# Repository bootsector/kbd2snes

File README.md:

# kbd2snes
PS/2 keyboard to Super Nintendo Adapter

http://www.brunofreitas.com/node/71

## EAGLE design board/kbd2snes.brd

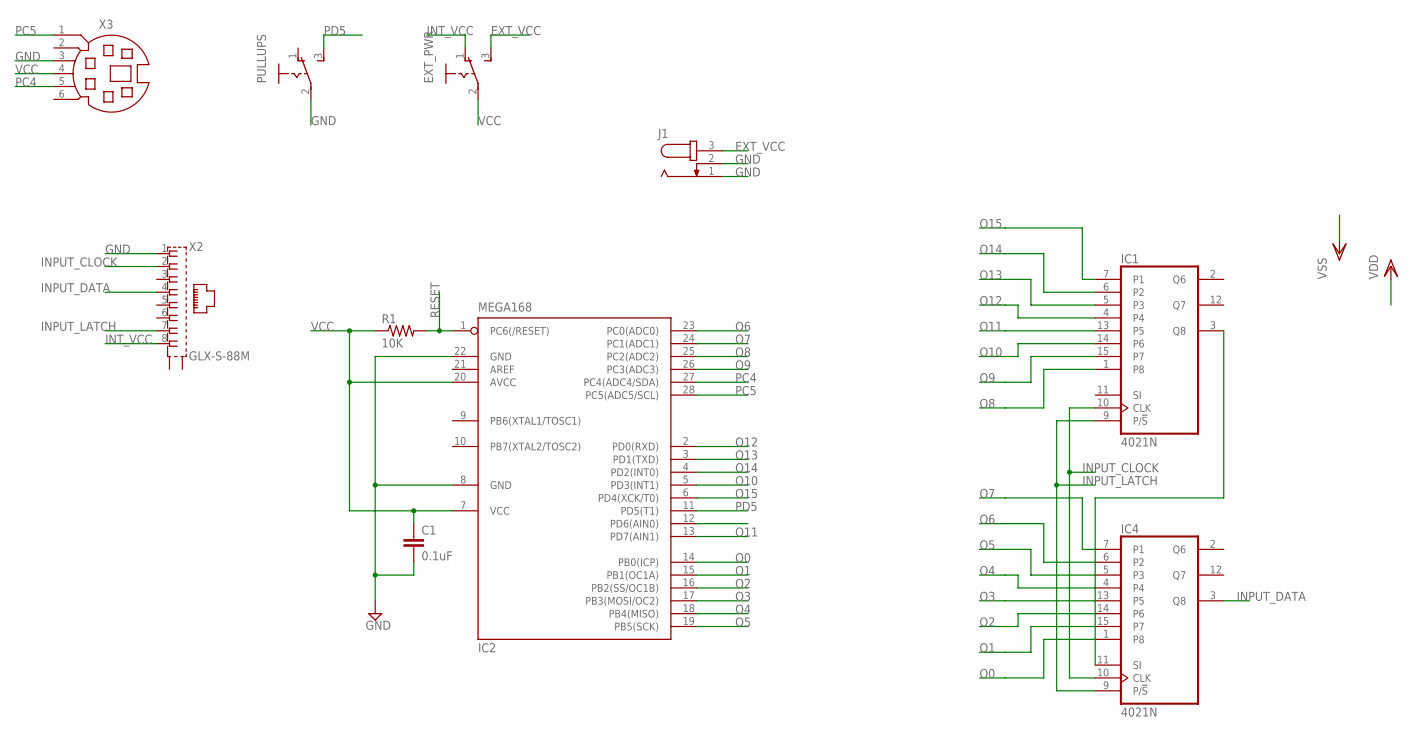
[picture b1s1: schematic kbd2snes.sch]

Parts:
C1: 0.1uF; C050-024X044
EXT_PWR: CHAVE
IC1, IC4: 4021N; DIL16
IC2: MEGA168; DIL28-3
J1: JACK-PLUG1; SPC4078
PULLUPS: CHAVE
R1: 10K; 0207/7
X2: GLX-S-88M
X3: MD06SS; MDIN06SS

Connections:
EXT_VCC: EXT_PWR.3 (S), J1.3
GND: C1.2, IC1.8 (VSS), IC2.8 (GND), IC2.22 (GND), IC4.8 (VSS), J1.1, J1.2, PULLUPS.2, X2.1, X3.3
INPUT_CLOCK: IC1.10 (CLK), IC4.10 (CLK), X2.2
INPUT_DATA: IC4.3 (Q8), X2.4
INPUT_LATCH: IC1.9 (P/!S), IC4.9 (P/!S), X2.7
INT_VCC: EXT_PWR.1 (O), X2.8
unnamed: IC1.3 (Q8), IC4.11 (SI)
O0: IC2.14 (PB0(ICP)), IC4.1 (P8)
O1: IC2.15 (PB1(OC1A)), IC4.15 (P7)
O2: IC2.16 (PB2(SS/OC1B)), IC4.14 (P6)
O3: IC2.17 (PB3(MOSI/OC2)), IC4.13 (P5)
O4: IC2.18 (PB4(MISO)), IC4.4
O5: IC2.19 (PB5(SCK)), IC4.5 (P3)
O6: IC2.23 (PC0(ADC0)), IC4.6 (P2)
O7: IC2.24 (PC1(ADC1)), IC4.7 (P1)
O8: IC1.1 (P8), IC2.25 (PC2(ADC2))
O9: IC1.15 (P7), IC2.26 (PC3(ADC3))
O10: IC1.14 (P6), IC2.5 (PD3(INT1))
O11: IC1.13 (P5), IC2.13 (PD7(AIN1))
O12: IC1.4, IC2.2 (PD0(RXD))
O13: IC1.5 (P3), IC2.3 (PD1(TXD))
O14: IC1.6 (P2), IC2.4 (PD2(INT0))
O15: IC1.7 (P1), IC2.6 (PD4(XCK/T0))
PC4: IC2.27 (PC4(ADC4/SDA)), X3.5
PC5: IC2.28 (PC5(ADC5/SCL)), X3.1
PD5: IC2.11 (PD5(T1)), PULLUPS.3 (S)
RESET: IC2.1 (PC6(/RESET)), R1.2
VCC: C1.1, EXT_PWR.2, IC1.16 (VDD), IC2.7 (VCC), IC2.20 (AVCC), IC4.16 (VDD), R1.1, X3.4

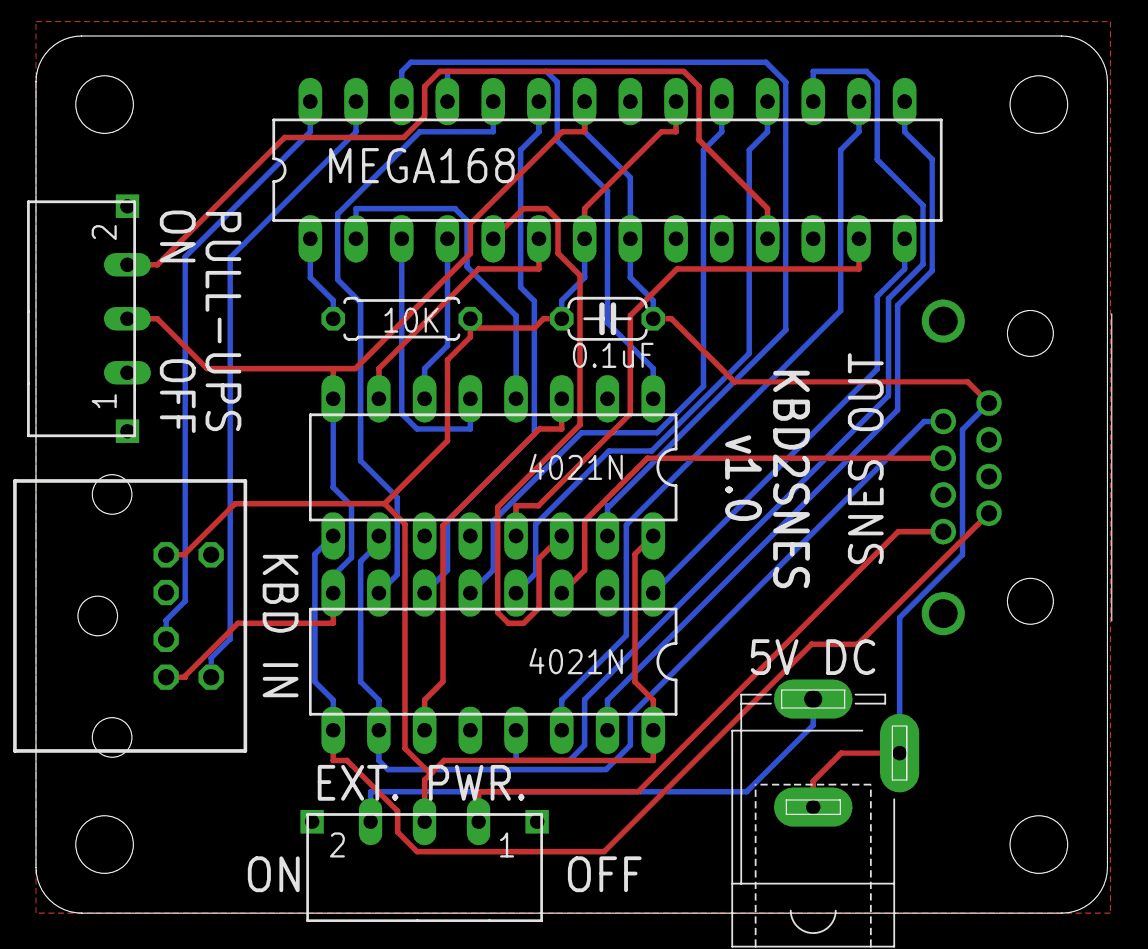
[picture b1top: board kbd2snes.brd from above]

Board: 2 copper layers, 59.8 x 48.7 mm, 10 parts (0 on the bottom side), 28 nets.

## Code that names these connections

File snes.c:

/*
 * KBD2SNES - PS/2 Keyboard Adapter for SNES
 * Copyright (c) 2016 Bruno Freitas - bruno@brunofreitas.com
 *
 * This program is free software: you can redistribute it and/or modify
 * it under the terms of the GNU General Public License as published by
 * the Free Software Foundation, either version 3 of the License, or
 * (at your option) any later version.
 *
 * This program is distributed in the hope that it will be useful,
 * but WITHOUT ANY WARRANTY; without even the implied warranty of
 * MERCHANTABILITY or FITNESS FOR A PARTICULAR PURPOSE.  See the
 * GNU General Public License for more details.
 *
 * You should have received a copy of the GNU General Public License
 * along with this program.  If not, see <http://www.gnu.org/licenses/>.
 */

#include <avr/io.h>

#include "snes.h"
#include "util.h"

void snes_init(void) {
	bit_set(DDRB, _BV(PB0));
	bit_set(DDRB, _BV(PB1));
	bit_set(DDRB, _BV(PB2));
	bit_set(DDRB, _BV(PB3));
	bit_set(DDRB, _BV(PB4));
	bit_set(DDRB, _BV(PB5));
	bit_set(DDRC, _BV(PC0));
	bit_set(DDRC, _BV(PC1));
	bit_set(DDRC, _BV(PC2));
	bit_set(DDRC, _BV(PC3));
	bit_set(DDRD, _BV(PD3));
	bit_set(DDRD, _BV(PD7));
	bit_set(DDRD, _BV(PD0));
	bit_set(DDRD, _BV(PD1));
	bit_set(DDRD, _BV(PD2));
	bit_set(DDRD, _BV(PD4));

	snes_reset_output();
}

void snes_reset_output(void) {
	bit_set(PORTB, _BV(PB0));
	bit_set(PORTB, _BV(PB1));
	bit_set(PORTB, _BV(PB2));
	bit_set(PORTB, _BV(PB3));
	bit_set(PORTB, _BV(PB4));
	bit_set(PORTB, _BV(PB5));
	bit_set(PORTC, _BV(PC0));
	bit_set(PORTC, _BV(PC1));
	bit_set(PORTC, _BV(PC2));
	bit_set(PORTC, _BV(PC3));
	bit_set(PORTD, _BV(PD3));
	bit_set(PORTD, _BV(PD7));
	bit_set(PORTD, _BV(PD0));
	bit_set(PORTD, _BV(PD1));
	bit_set(PORTD, _BV(PD2));
	bit_set(PORTD, _BV(PD4));
}

void snes_press(uint8_t button) {
	switch(button) {
		case SNES_B:
			bit_clear(PORTB, _BV(PB0));
			break;
		case SNES_Y:
			bit_clear(PORTB, _BV(PB1));
			break;
		case SNES_SELECT:
			bit_clear(PORTB, _BV(PB2));
			break;
		case SNES_START:
			bit_clear(PORTB, _BV(PB3));
			break;
		case SNES_UP:
			//snes_release(SNES_DOWN);
			bit_clear(PORTB, _BV(PB4));
			break;
		case SNES_DOWN:
			//snes_release(SNES_UP);
			bit_clear(PORTB, _BV(PB5));
			break;
		case SNES_LEFT:
			//snes_release(SNES_RIGHT);
			bit_clear(PORTC, _BV(PC0));
			break;
		case SNES_RIGHT:
			//snes_release(SNES_LEFT);
			bit_clear(PORTC, _BV(PC1));
			break;
		case SNES_A:
			bit_clear(PORTC, _BV(PC2));
			break;
		case SNES_X:
			bit_clear(PORTC, _BV(PC3));
			break;
		case SNES_L:
			bit_clear(PORTD, _BV(PD3));
			break;
		case SNES_R:
			bit_clear(PORTD, _BV(PD7));
			break;
		case SNES_XTRA_1:
			bit_clear(PORTD, _BV(PD0));
			break;
		case SNES_XTRA_2:
			bit_clear(PORTD, _BV(PD1));
			break;
		case SNES_XTRA_3:
			bit_clear(PORTD, _BV(PD2));
			break;
		case SNES_XTRA_4:
			bit_clear(PORTD, _BV(PD4));
			break;
	}
}

void snes_release(uint8_t button) {
	switch(button) {
		case SNES_B:
			bit_set(PORTB, _BV(PB0));
			break;
		case SNES_Y:
			bit_set(PORTB, _BV(PB1));
			break;
		case SNES_SELECT:
			bit_set(PORTB, _BV(PB2));
			break;
		case SNES_START:
			bit_set(PORTB, _BV(PB3));
			break;
		case SNES_UP:
			bit_set(PORTB, _BV(PB4));
			break;
		case SNES_DOWN:
			bit_set(PORTB, _BV(PB5));
			break;
		case SNES_LEFT:
			bit_set(PORTC, _BV(PC0));
			break;
		case SNES_RIGHT:
			bit_set(PORTC, _BV(PC1));
			break;
		case SNES_A:
			bit_set(PORTC, _BV(PC2));
			break;
		case SNES_X:
			bit_set(PORTC, _BV(PC3));
			break;
		case SNES_L:
			bit_set(PORTD, _BV(PD3));
			break;
		case SNES_R:
			bit_set(PORTD, _BV(PD7));
			break;
		case SNES_XTRA_1:
			bit_set(PORTD, _BV(PD0));
			break;
		case SNES_XTRA_2:
			bit_set(PORTD, _BV(PD1));
			break;
		case SNES_XTRA_3:
			bit_set(PORTD, _BV(PD2));
			break;
		case SNES_XTRA_4:
			bit_set(PORTD, _BV(PD4));
			break;
	}
}

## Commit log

2016-02-10 Initial code push
2016-02-10 Cleanup
2016-02-11 Returns a known value (zero) if reading an empty buffer
2016-02-11 Add gnu99 compile flag
2016-02-11 Keyboard reading driver. Tests pending...
2016-02-11 Added snes output driver
2016-02-11 Renamed Makefile
2016-02-11 Suggested conversion
2016-02-11 Added keyboard to snes translation code. Tests pending.
2016-02-11 Code cleanup
2016-02-11 Disabled internal pullups. It looks like keyboards already have them. Tests pending...
2016-02-11 Makefile changes
2016-02-11 Added GPL disclaimer
2016-02-12 Initial tests passed. It does not seem to work under 3.3v
2016-02-12 Added board Eagle files
2016-02-12 Refactored keyboard polling mechanism to implement lookup tables. This way, we can have several key profiles
2016-02-12 Fixed kbd profiles. Added a new profile. Added support to profile selection by pressing F1 key
2016-02-12 Reset SNES output when switching keyboard input profiles
2016-02-12 Minor change at main.c
2016-02-13 Added bit_set and bit_clear macros
2016-02-15 Detect large clock change gaps and resync
2016-02-16 Changed second profile. Added ENTER key as START
2016-02-16 Refactoring - Added ringbuffer.c as part of the keyboard driver - kbd.c
2016-02-17 Added pullup on-off switch control
2016-02-17 Mapped extra pins on CD4021 (O12-O15) to extra keys
2016-02-17 Added scancodes 2 reference
2016-02-19 Removed SNES impossible keys output limitation
2016-03-22 Removed test code
